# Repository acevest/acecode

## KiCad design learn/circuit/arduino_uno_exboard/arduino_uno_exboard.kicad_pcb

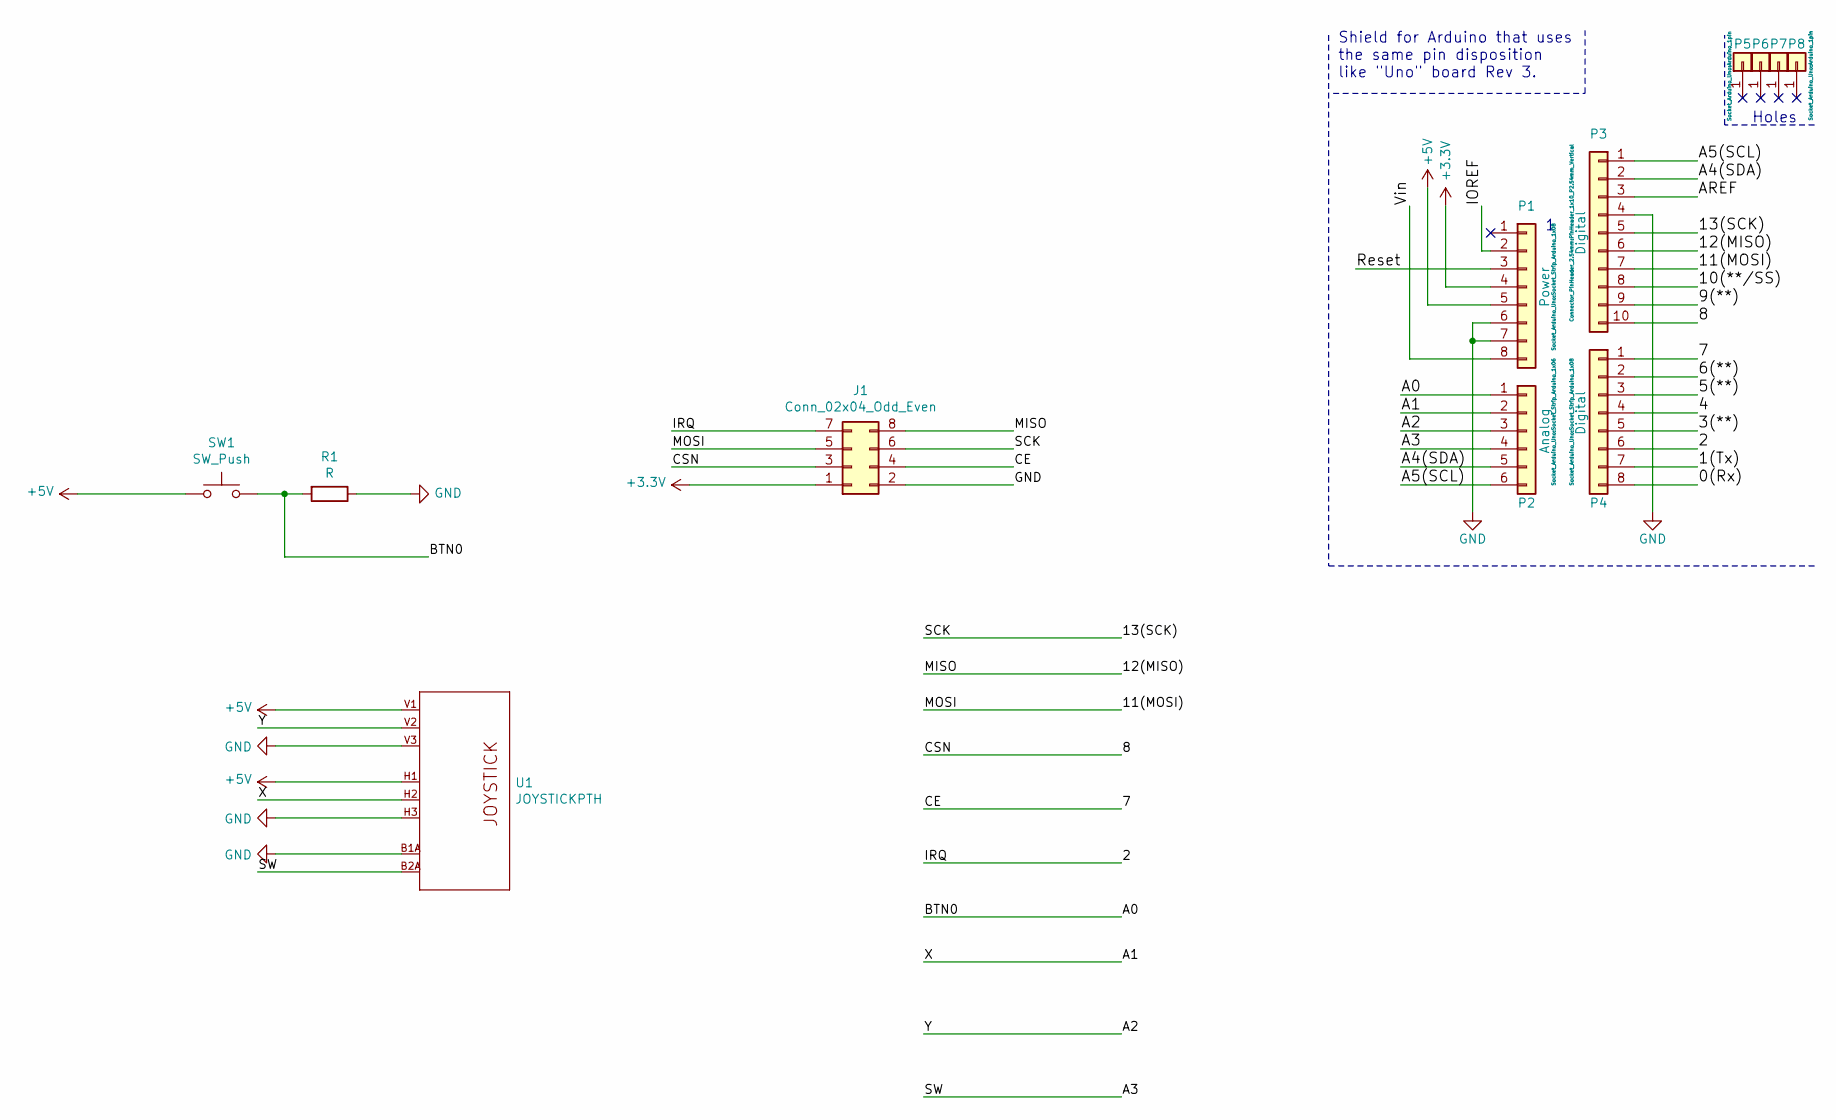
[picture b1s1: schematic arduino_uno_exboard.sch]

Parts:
J1: Conn_02x04_Odd_Even; PinSocket_2x04_P2.54mm_Vertical
P1: Power; Socket_Strip_Arduino_1x08
P2: Analog; Socket_Strip_Arduino_1x06
P3: Digital; PinHeader_1x10_P2.54mm_Vertical
P4: Digital; Socket_Strip_Arduino_1x08
P5, P6, P7, P8: CONN_01X01; Arduino_1pin
R1: R; R_Axial_DIN0207_L6.3mm_D2.5mm_P10.16mm_Horizontal
SW1: SW_Push; SW_PUSH-12mm
U1: JOYSTICKPTH; JOYSTICK

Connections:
+3V3: J1.1, P1.4
+5V: P1.5, SW1.1, U1.H1 (H+), U1.V1 (V+); also elsewhere on the board
/0(Rx): P4.8
/1(Tx): P4.7
/2: J1.7, P4.6
/3(**): P4.5
/4: P4.4
/5(**): P4.3
/6(**): P4.2
/7: J1.4, P4.1
/8: J1.3, P3.10
/9(**): P3.9
/10(**/SS): P3.8
/11(MOSI): J1.5, P3.7
/12(MISO): J1.8, P3.6
/13(SCK): J1.6, P3.5
/A0: P2.1, R1.2, SW1.2; also elsewhere on the board
/A1: P2.2, U1.H2 (H)
/A2: P2.3, U1.V2 (V)
/A3: P2.4, U1.B2A (SEL-)
/A4(SDA): P2.5, P3.2
/A5(SCL): P2.6, P3.1
/AREF: P3.3
/IOREF: P1.2
/Reset: P1.3
/Vin: P1.8
GND: J1.2, P1.6, P1.7, P3.4, R1.1, U1.B1A (SEL+), U1.H3 (H-), U1.V3 (V-)

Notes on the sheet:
Holes
Shield for Arduino that uses the same pin disposition like "Uno" board Rev 3.

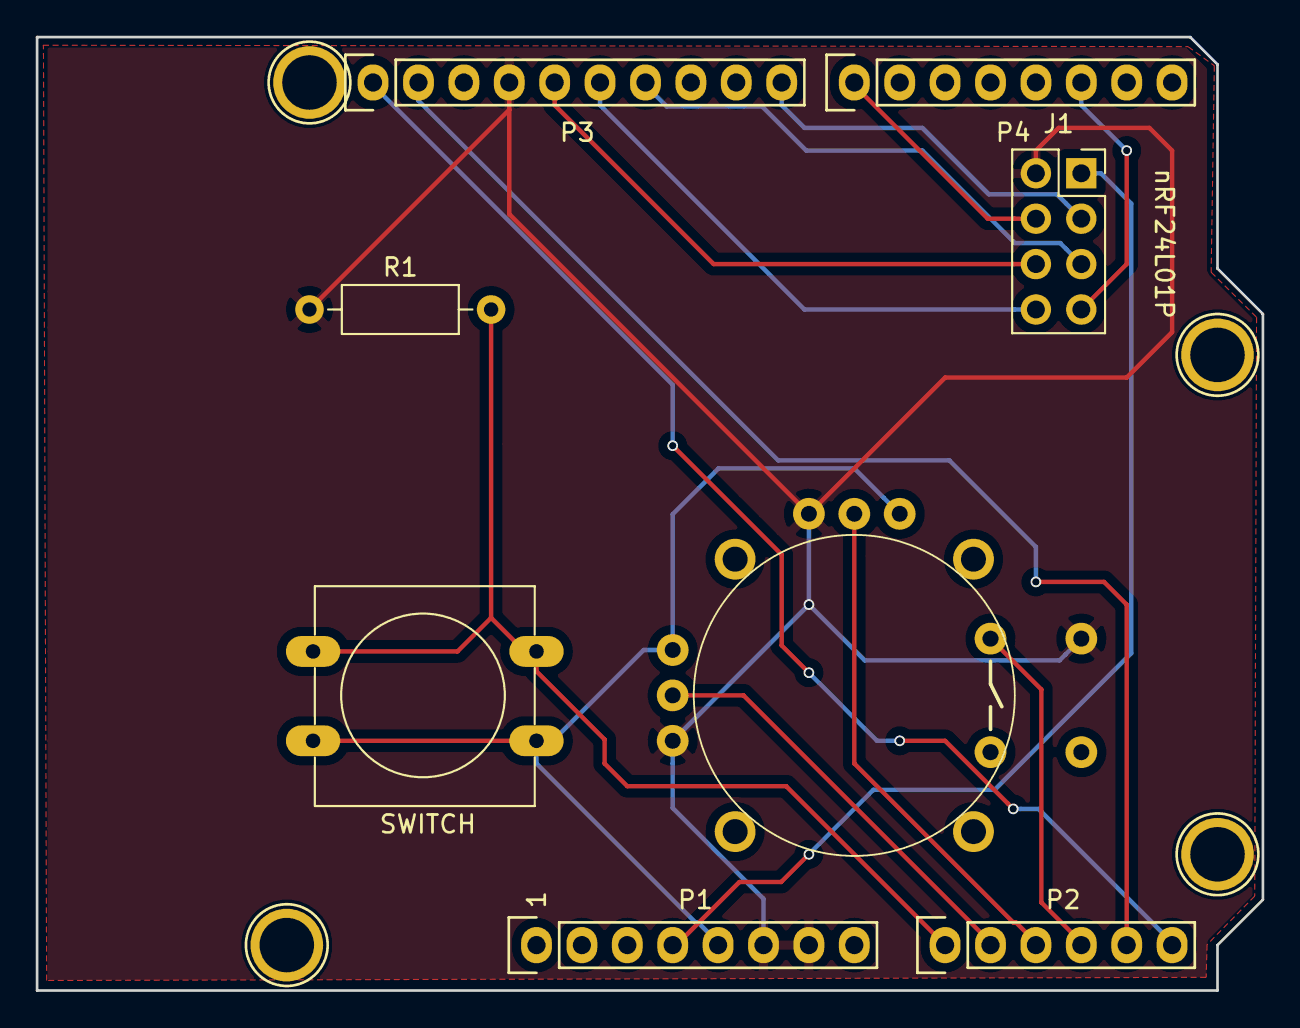
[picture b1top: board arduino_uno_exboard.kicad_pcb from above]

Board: 2 copper layers, 68.6 x 53.3 mm, 12 parts (0 on the bottom side), 15 nets.

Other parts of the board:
SWITCH: SW_Push; SW_PUSH-12mm

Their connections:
+5V: SWITCH.1; also elsewhere on the board
/A0: SWITCH.2; also elsewhere on the board

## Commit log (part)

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2015-07-27 ignore ish
2015-07-28 del .DS_Store
2015-07-29 test md
2015-09-02 add ruby in cs
2015-10-03 add mysqlinjection.md
2015-10-09 add tmux.conf
2015-11-13 go...
2015-11-14 learn go
2015-11-17 Create gh-pages branch via GitHub
2015-11-28 learn go...
2015-11-28 learn go ...
2016-03-09 hehe
2016-03-09 change tab bar item colour
2016-03-11 add icon
2016-06-17 add AcePlay
2016-06-19 swift:functions & closures
2016-06-19 closure
2016-06-22 enumerations
2016-06-22 Classes & Properties
2016-07-04 swift convert
2016-07-04 add get_lan_ip
2016-07-20 add 0day 3.2 shellcode
2016-07-21 add asm2scs.py
2016-07-24 add shellcode
2016-08-01 add sqlinject tool
2016-09-25 add jp
2016-11-06 convert swift from 2.2 to 3.0
2016-11-19 add foodtracker
2017-03-14 swift-subscripts
2017-03-14 swift-Inheritance-Initialization
2017-03-16 Swift - Initialization
2017-03-19 Swift - Deinitialization ARC OptionalChaining
2017-03-19 Swift - ErrorHandling TypeCasting NestedTypes Extensions Protocols
2017-03-26 Swift - Generics AddvancedOperators
2017-04-03 mac_bash_profile-go
2017-04-03 mbp bash profile
2017-04-24 linux bash profile
2017-06-05 add <<The Go Programming Language Exercise
2017-07-23 ksp tool
2018-05-22 add u8g2_chinese_font_maker
2018-06-14 add ace arduino hardware
2018-06-15 atemga328p avr code
2018-06-15 clean codes
2018-06-20 add rtos
2018-06-20 mac bash profile
2018-06-25 add menuconfig
2018-11-30 add gps transfer tool
2018-12-11 add logger
2019-03-03 add arduino old code
2019-03-27 add vim plugin document
2019-03-27 add port forward
2019-04-05 bash
2019-05-19 add stm32
2019-05-25 add system clock
2019-05-27 SysTick Delay
2019-06-01 F103HAL
2019-06-01 F103HAL-支持Serial Wire调式
2019-06-01 F103HAL-compile link debug
2019-06-01 F103HAL gpio output open drain mode
2019-06-01 SysClk手动设置为72MHz，时钟切为外部高速时钟HSE
2019-06-01 F103HAL SysTick
2019-06-03 USART.md
2019-06-04 add stm32f103re
2019-06-05 F103RE GPIO
2019-06-05 F103RE GPIO KEY1 INPUT
2019-06-05 F103RE GPIO Input Interrupt
2019-06-07 usart1 usart2 之间重定向
2019-06-17 usart1 usart2 dma 转发
2019-07-03 usart dma variable receive length
2019-12-23 add zshrc
2020-01-19 add bit pic tool
2020-09-22 cs time style
2020-11-23 rust helloworld
2020-11-23 hello_cargo
2021-01-17 add esp32cam arduino code
2021-01-17 add esp32camweb
2021-01-17 add audio player web
2021-08-30 learn rust: guessing_game
2021-09-21 add rust owner ship
2021-10-30 add keyboard_interrupt.asm
2021-11-23 add go abstract factory
2021-12-12 cs add support for S
